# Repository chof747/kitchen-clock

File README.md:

# Kitchen Clock Project

This project is building a kitchen glock with the following functions:

- Servo driven largely visible glock gauge
- Alarm functions that can be sequenced easily
- Temperature control of a stove or oven
- Integration into home automation systems with HA and/or MQTT
- Ringing alarm function

the project will contain all the necessary electrical and housing components.

## PCB

**v1.0**: Initial version of PCB sent to production on 22.07.2024
**v1.1**

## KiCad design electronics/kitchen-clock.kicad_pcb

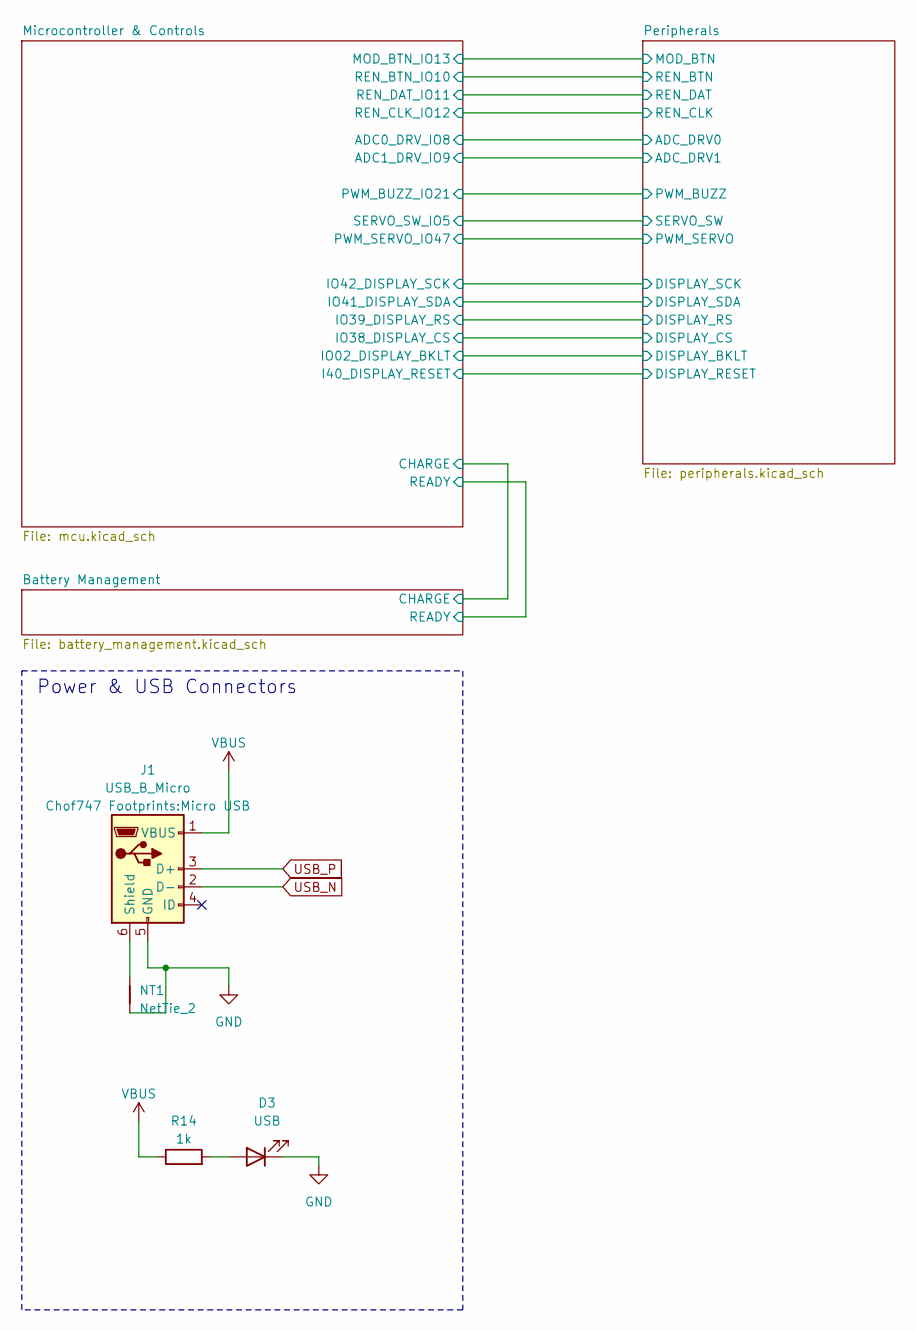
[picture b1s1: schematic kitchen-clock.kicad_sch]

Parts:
D3: USB; LED_D3.0mm
J1: USB_B_Micro; Micro USB
NT1: NetTie_2; NetTie-2_SMD_Pad0.5mm
R14: 1k; R_0603_1608Metric_Pad0.98x0.95mm_HandSolder

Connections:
GND: D3.1 (K), J1.5 (GND), NT1.1; also elsewhere on the board
unnamed: D3.2 (A), R14.2
unnamed: J1.6 (Shield), NT1.2
USB_N: J1.2 (D-); also elsewhere on the board
USB_P: J1.3 (D+); also elsewhere on the board
VBUS: J1.1 (VBUS), R14.1; also elsewhere on the board

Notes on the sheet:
Power & USB Connectors

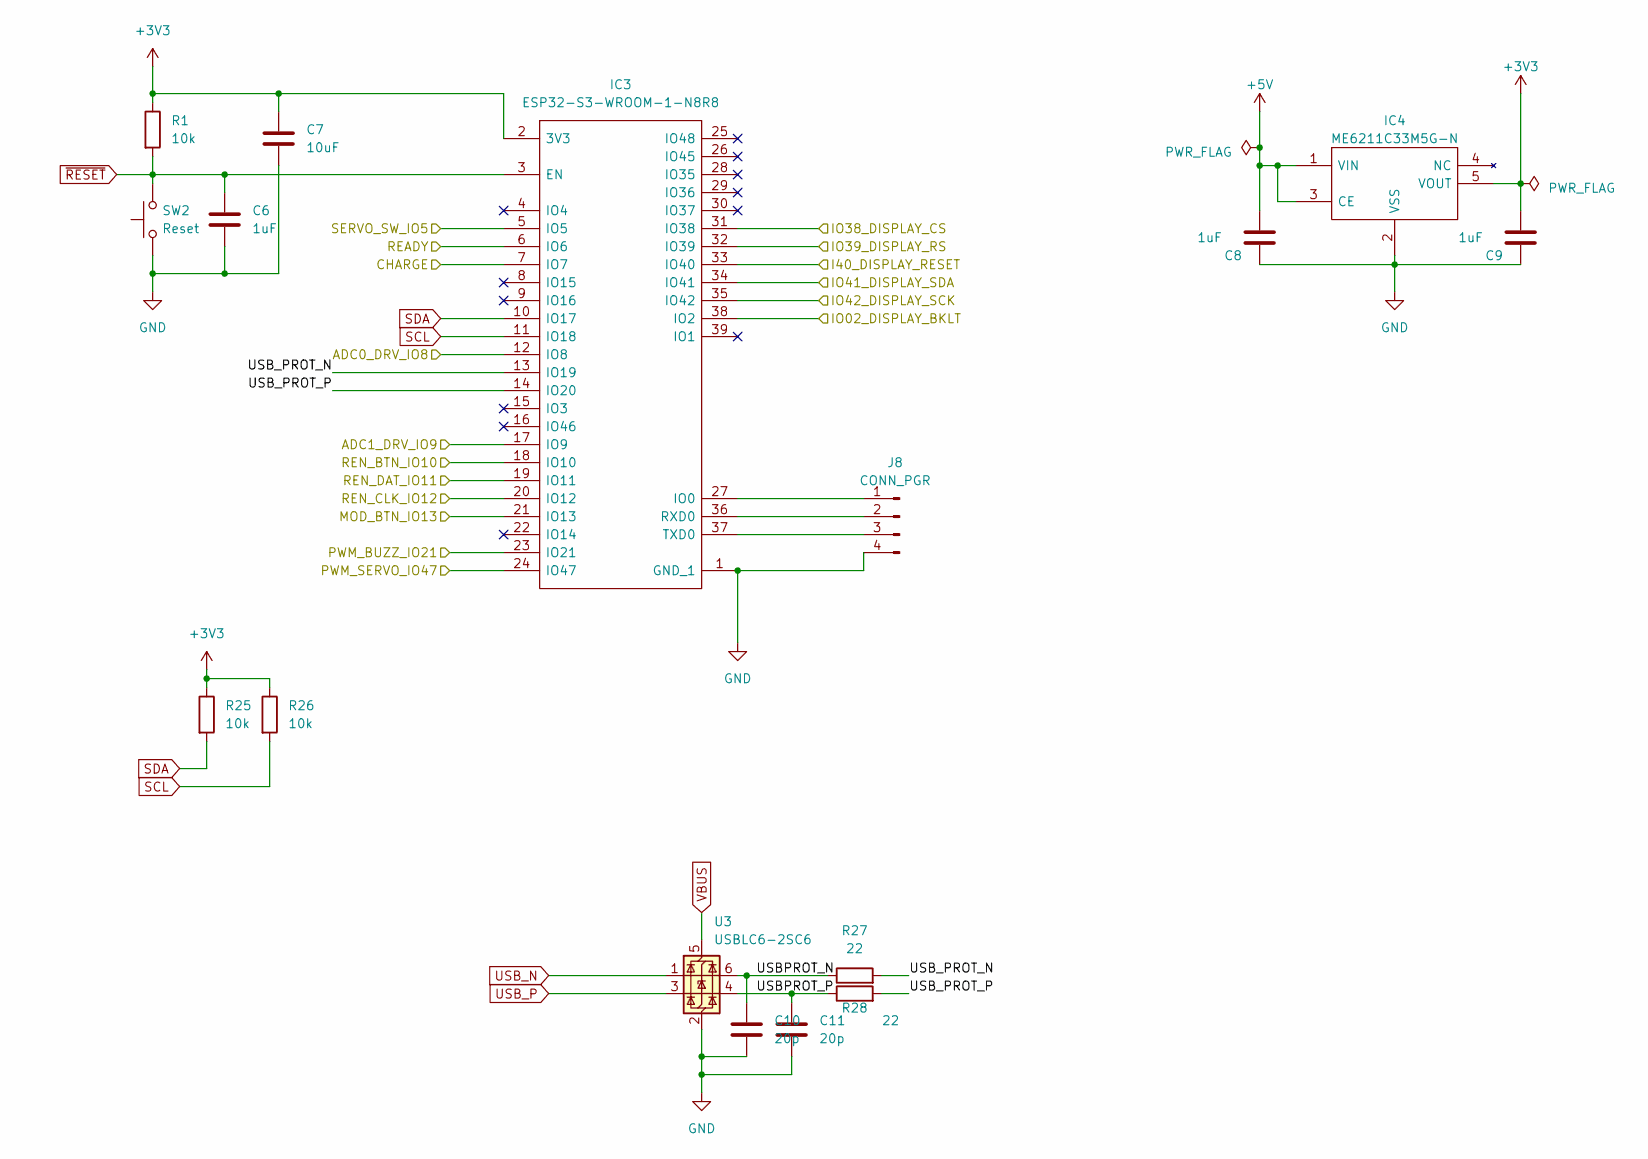
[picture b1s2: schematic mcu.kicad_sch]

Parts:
C6, C8, C9: 1uF; C_0603_1608Metric_Pad1.08x0.95mm_HandSolder
C7: 10uF; C_0603_1608Metric_Pad1.08x0.95mm_HandSolder
C10, C11: 20p; C_0603_1608Metric_Pad1.08x0.95mm_HandSolder
IC3: ESP32-S3-WROOM-1-N8R8; ESP32S3WROOM1N8R8; Manufacturer_Part_Number ESP32-S3-WROOM-1-N8R8; Mouser Part Number 356-EP32S3WROOM1N8R8
IC4: ME6211C33M5G-N; SOT95P270X145-5N; Manufacturer_Part_Number ME6211C33M5G-N
J8: CONN_PGR; PinSocket_1x04_P2.54mm_Vertical
R1, R25, R26: 10k; R_0603_1608Metric_Pad0.98x0.95mm_HandSolder
R27, R28: 22; R_0603_1608Metric_Pad0.98x0.95mm_HandSolder
SW2: Reset; 1TS003B-2500-3500A-CT (SMD Right Angle Tactile Switch)
U3: USBLC6-2SC6; SOT-23-6

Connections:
+3V3: C7.1, C9.1, IC3.2 (3V3), IC4.5 (VOUT), R1.1, R25.1, R26.1; also elsewhere on the board
+5V: C8.1, IC4.1 (VIN), IC4.3 (CE); also elsewhere on the board
/Battery Management/CHARGE: IC3.7 (IO7); also elsewhere on the board
/Battery Management/READY: IC3.6 (IO6); also elsewhere on the board
/Microcontroller & Controls/ADC0_DRV_IO8: IC3.12 (IO8); also elsewhere on the board
/Microcontroller & Controls/ADC1_DRV_IO9: IC3.17 (IO9); also elsewhere on the board
/Microcontroller & Controls/I40_DISPLAY_RESET: IC3.33 (IO40); also elsewhere on the board
/Microcontroller & Controls/IO02_DISPLAY_BKLT: IC3.38 (IO2); also elsewhere on the board
/Microcontroller & Controls/IO38_DISPLAY_CS: IC3.31 (IO38); also elsewhere on the board
/Microcontroller & Controls/IO39_DISPLAY_RS: IC3.32 (IO39); also elsewhere on the board
/Microcontroller & Controls/IO41_DISPLAY_SDA: IC3.34 (IO41); also elsewhere on the board
/Microcontroller & Controls/IO42_DISPLAY_SCK: IC3.35 (IO42); also elsewhere on the board
/Microcontroller & Controls/MOD_BTN_IO13: IC3.21 (IO13); also elsewhere on the board
/Microcontroller & Controls/PWM_BUZZ_IO21: IC3.23 (IO21); also elsewhere on the board
/Microcontroller & Controls/PWM_SERVO_IO47: IC3.24 (IO47); also elsewhere on the board
/Microcontroller & Controls/REN_BTN_IO10: IC3.18 (IO10); also elsewhere on the board
/Microcontroller & Controls/REN_CLK_IO12: IC3.20 (IO12); also elsewhere on the board
/Microcontroller & Controls/REN_DAT_IO11: IC3.19 (IO11); also elsewhere on the board
/Microcontroller & Controls/SERVO_SW_IO5: IC3.5 (IO5); also elsewhere on the board
/Microcontroller & Controls/USBPROT_N: C10.1, R27.1, U3.6 (I/O1)
/Microcontroller & Controls/USBPROT_P: C11.1, R28.1, U3.4 (I/O2)
/Microcontroller & Controls/USB_PROT_N: IC3.13 (IO19), R27.2
/Microcontroller & Controls/USB_PROT_P: IC3.14 (IO20), R28.2
GND: C6.2, C7.2, C8.2, C9.2, C10.2, C11.2, IC3.1 (GND_1), IC4.2 (VSS), J8.4, SW2.1, U3.2 (GND); also elsewhere on the board
unnamed: IC3.27 (IO0), J8.1
unnamed: IC3.36 (RXD0), J8.2
unnamed: IC3.37 (TXD0), J8.3
SCL: IC3.11 (IO18), R26.2; also elsewhere on the board
SDA: IC3.10 (IO17), R25.2; also elsewhere on the board
USB_N: U3.1 (I/O1); also elsewhere on the board
USB_P: U3.3 (I/O2); also elsewhere on the board
VBUS: U3.5 (VBUS); also elsewhere on the board
~RESET: C6.1, IC3.3 (EN), R1.2, SW2.2; also elsewhere on the board

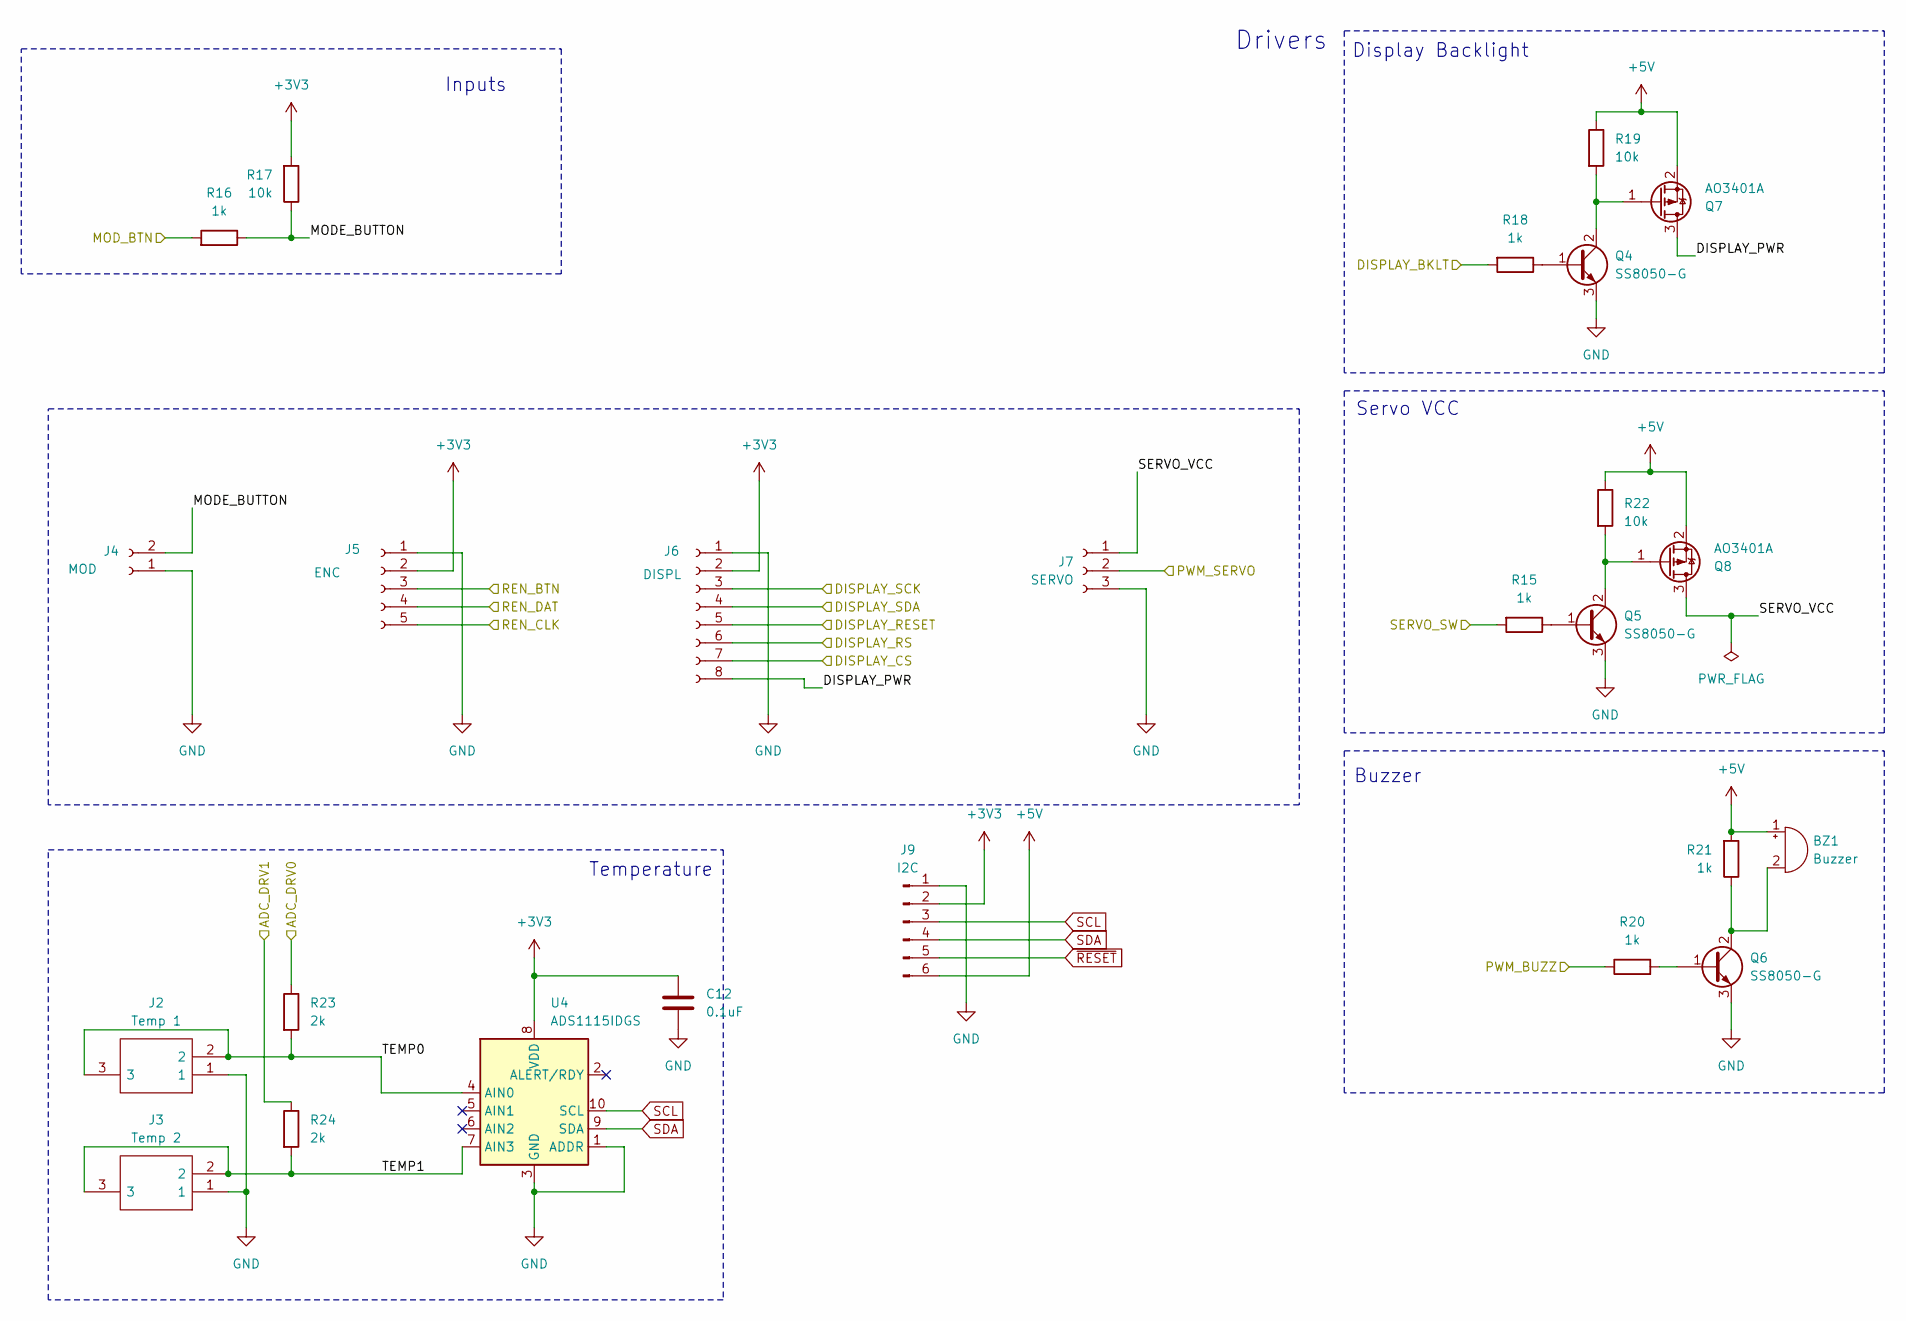
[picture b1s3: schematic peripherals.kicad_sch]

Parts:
BZ1: Buzzer; PS1240P02BT
C12: 0.1uF; C_0603_1608Metric_Pad1.08x0.95mm_HandSolder
J2: Temp 1; MJ2509N; Manufacturer_Part_Number MJ-2509N; Mouser Part Number 490-MJ-2509N
J3: Temp 2; MJ2509N; Manufacturer_Part_Number MJ-2509N; Mouser Part Number 490-MJ-2509N
J4: MOD; PinSocket_1x02_P2.54mm_Vertical
J5: ENC; PinSocket_1x05_P2.54mm_Vertical
J6: DISPL; PinSocket_1x08_P2.54mm_Vertical
J7: SERVO; PinSocket_1x03_P2.54mm_Vertical
J9: I2C; PinHeader_1x06_P2.54mm_Vertical
Q4, Q5, Q6: SS8050-G; SOT-23
Q7, Q8: AO3401A; SOT-23
R15, R16, R18, R20, R21: 1k; R_0603_1608Metric_Pad0.98x0.95mm_HandSolder
R17, R19, R22: 10k; R_0603_1608Metric_Pad0.98x0.95mm_HandSolder
R23, R24: 2k; R_0603_1608Metric_Pad0.98x0.95mm_HandSolder
U4: ADS1115IDGS; TSSOP-10_3x3mm_P0.5mm

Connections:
+3V3: C12.1, J5.2, J6.2, J9.2, R17.2, U4.8 (VDD); also elsewhere on the board
+5V: BZ1.1 (+), J9.6, Q7.2 (S), Q8.2 (S), R19.1, R21.2, R22.1; also elsewhere on the board
/Microcontroller & Controls/ADC0_DRV_IO8: R23.1; also elsewhere on the board
/Microcontroller & Controls/ADC1_DRV_IO9: R24.1; also elsewhere on the board
/Microcontroller & Controls/I40_DISPLAY_RESET: J6.5; also elsewhere on the board
/Microcontroller & Controls/IO02_DISPLAY_BKLT: R18.2; also elsewhere on the board
/Microcontroller & Controls/IO38_DISPLAY_CS: J6.7; also elsewhere on the board
/Microcontroller & Controls/IO39_DISPLAY_RS: J6.6; also elsewhere on the board
/Microcontroller & Controls/IO41_DISPLAY_SDA: J6.4; also elsewhere on the board
/Microcontroller & Controls/IO42_DISPLAY_SCK: J6.3; also elsewhere on the board
/Microcontroller & Controls/MOD_BTN_IO13: R16.2; also elsewhere on the board
/Microcontroller & Controls/PWM_BUZZ_IO21: R20.1; also elsewhere on the board
/Microcontroller & Controls/PWM_SERVO_IO47: J7.2; also elsewhere on the board
/Microcontroller & Controls/REN_BTN_IO10: J5.3; also elsewhere on the board
/Microcontroller & Controls/REN_CLK_IO12: J5.5; also elsewhere on the board
/Microcontroller & Controls/REN_DAT_IO11: J5.4; also elsewhere on the board
/Microcontroller & Controls/SERVO_SW_IO5: R15.2; also elsewhere on the board
/Peripherals/DISPLAY_PWR: J6.8, Q7.3 (D)
/Peripherals/MODE_BUTTON: J4.2, R16.1, R17.1
/Peripherals/SERVO_VCC: J7.1, Q8.3 (D)
/Peripherals/TEMP0: J2.2, J2.3, R23.2, U4.4 (AIN0)
/Peripherals/TEMP1: J3.2, J3.3, R24.2, U4.7 (AIN3)
GND: C12.2, J2.1, J3.1, J4.1, J5.1, J6.1, J7.3, J9.1, Q4.3 (E), Q5.3 (E), Q6.3 (E), U4.1 (ADDR), U4.3 (GND); also elsewhere on the board
unnamed: BZ1.2 (-), Q6.2 (C), R21.1
unnamed: Q4.1 (B), R18.1
unnamed: Q4.2 (C), Q7.1 (G), R19.2
unnamed: Q5.1 (B), R15.1
unnamed: Q5.2 (C), Q8.1 (G), R22.2
unnamed: Q6.1 (B), R20.2
SCL: J9.3, U4.10 (SCL); also elsewhere on the board
SDA: J9.4, U4.9 (SDA); also elsewhere on the board
~RESET: J9.5; also elsewhere on the board

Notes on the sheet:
Temperature
Servo VCC
Inputs
Drivers
Buzzer
Display Backlight

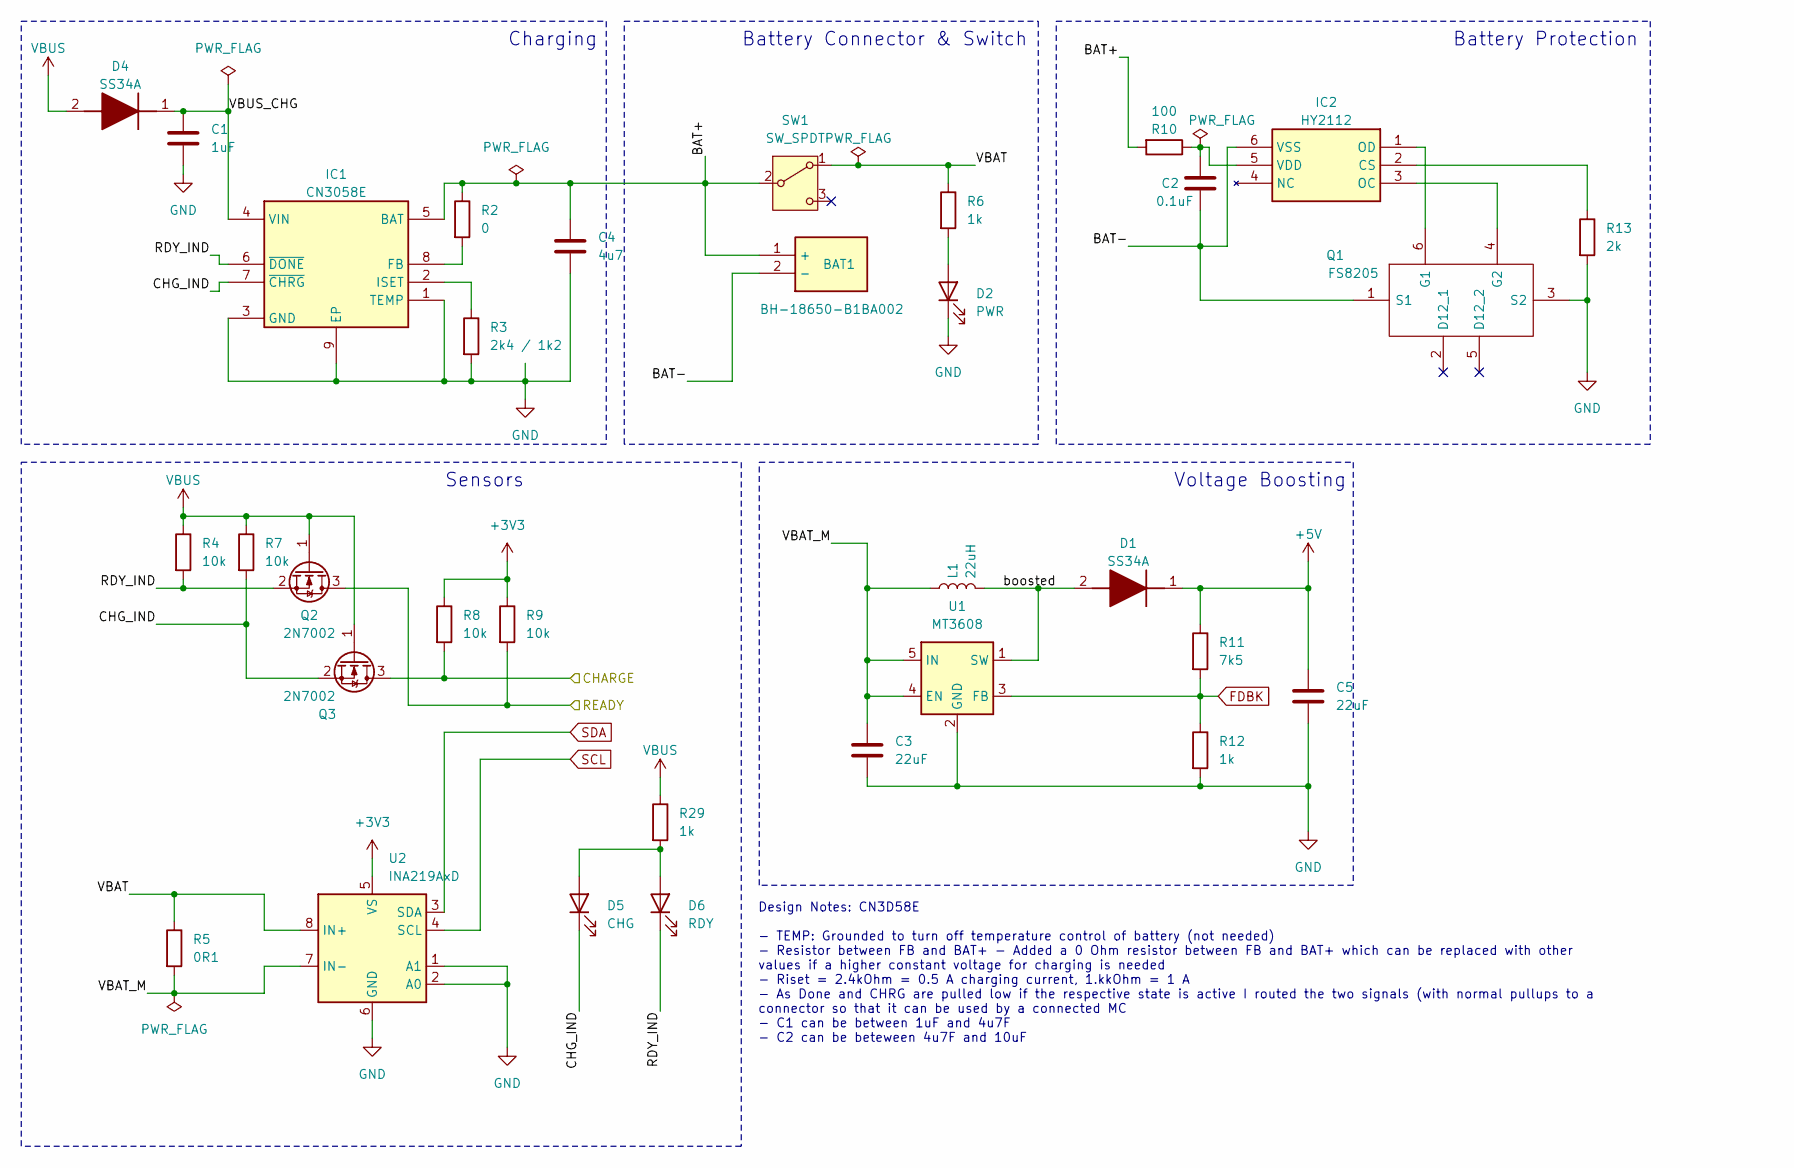
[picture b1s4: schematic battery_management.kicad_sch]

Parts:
BAT1: BH-18650-B1BA002; BH18650B1BA002; Manufacturer_Part_Number BH-18650-B1BA002
C1: 1uF; C_0603_1608Metric_Pad1.08x0.95mm_HandSolder
C2: 0.1uF; C_0603_1608Metric_Pad1.08x0.95mm_HandSolder
C3, C5: 22uF; C_1206_3216Metric_Pad1.33x1.80mm_HandSolder
C4: 4u7; C_0603_1608Metric_Pad1.08x0.95mm_HandSolder
D1, D4: SS34A; DIOM5026X262N; Manufacturer_Part_Number SS34A
D2: PWR; LED_D3.0mm
D5: CHG; LED_D3.0mm
D6: RDY; LED_D3.0mm
IC1: CN3058E; SOIC127P600X175-9N; Manufacturer_Part_Number CN3058E
IC2: HY2112; SOT95P280X145-6N; Manufacturer_Part_Number HY2112
L1: 22uH; SMD0740
Q1: FS8205; Manufacturer_Part_Number FS8205
Q2, Q3: 2N7002; SOT-23
R2: 0; R_0603_1608Metric_Pad0.98x0.95mm_HandSolder
R3: 2k4 / 1k2; R_0603_1608Metric_Pad0.98x0.95mm_HandSolder
R4, R7, R8, R9: 10k; R_0603_1608Metric_Pad0.98x0.95mm_HandSolder
R5: 0R1; R_2512_6332Metric_Pad1.40x3.35mm_HandSolder
R6, R12, R29: 1k; R_0603_1608Metric_Pad0.98x0.95mm_HandSolder
R10: 100; R_0603_1608Metric_Pad0.98x0.95mm_HandSolder
R11: 7k5; R_0603_1608Metric_Pad0.98x0.95mm_HandSolder
R13: 2k; R_0603_1608Metric_Pad0.98x0.95mm_HandSolder
SW1: SW_SPDT; Slide-switch-SS-12D11L7
U1: MT3608; SOT-23-6
U2: INA219AxD; SOIC-8_3.9x4.9mm_P1.27mm

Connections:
+3V3: R8.1, R9.1, U2.5 (VS); also elsewhere on the board
+5V: C5.1, D1.1 (K), R11.1; also elsewhere on the board
/Battery Management/BAT+: BAT1.1 (+), C4.1, IC1.5 (BAT), R2.1, R10.2, SW1.2 (B)
/Battery Management/BAT-: BAT1.2 (-), C2.2, IC2.6 (VSS), Q1.1 (S1)
/Battery Management/CHARGE: Q3.3 (D), R8.2; also elsewhere on the board
/Battery Management/CHG_IND: D5.1 (K), IC1.7 (~CHRG), Q3.2 (S), R7.2
/Battery Management/RDY_IND: D6.1 (K), IC1.6 (~DONE), Q2.2 (S), R4.2
/Battery Management/READY: Q2.3 (D), R9.2; also elsewhere on the board
/Battery Management/VBAT: R5.1, R6.1, SW1.1 (A), U2.8 (IN+)
/Battery Management/VBAT_M: C3.1, L1.1, R5.2, U1.4 (EN), U1.5 (IN), U2.7 (IN-)
/Battery Management/VBUS_CHG: C1.1, D4.1 (K), IC1.4 (VIN)
/Battery Management/boosted: D1.2 (A), L1.2, U1.1 (SW)
FDBK: R11.2, R12.1, U1.3 (FB)
GND: C1.2, C3.2, C4.2, C5.2, D2.1 (K), IC1.1 (TEMP), IC1.3 (GND), IC1.9 (EP), Q1.3 (S2), R3.2, R12.2, R13.2, U1.2 (GND), U2.1 (A1), U2.2 (A0), U2.6 (GND); also elsewhere on the board
unnamed: D2.2 (A), R6.2
unnamed: D5.2 (A), D6.2 (A), R29.2
unnamed: IC1.8 (FB), R2.2
unnamed: IC1.2 (ISET), R3.1
unnamed: IC2.2 (CS), R13.1
unnamed: IC2.3 (OC), Q1.4 (G2)
unnamed: IC2.1 (OD), Q1.6 (G1)
unnamed: C2.1, IC2.5 (VDD), R10.1
SCL: U2.4 (SCL); also elsewhere on the board
SDA: U2.3 (SDA); also elsewhere on the board
VBUS: D4.2 (A), Q2.1 (G), Q3.1 (G), R4.1, R7.1, R29.1; also elsewhere on the board

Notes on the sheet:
Design Notes: CN3D58E - TEMP: Grounded to turn off temperature control of battery (not needed) - Resistor between FB and BAT+ - Added a 0 Ohm resistor between FB and BAT+ which can be replaced with other values if a higher constant voltage for charging is needed - Riset = 2.4kOhm = 0.5 A charging c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
Battery Protection
Battery Connector & Switch
Voltage Boosting
Charging
Sensors

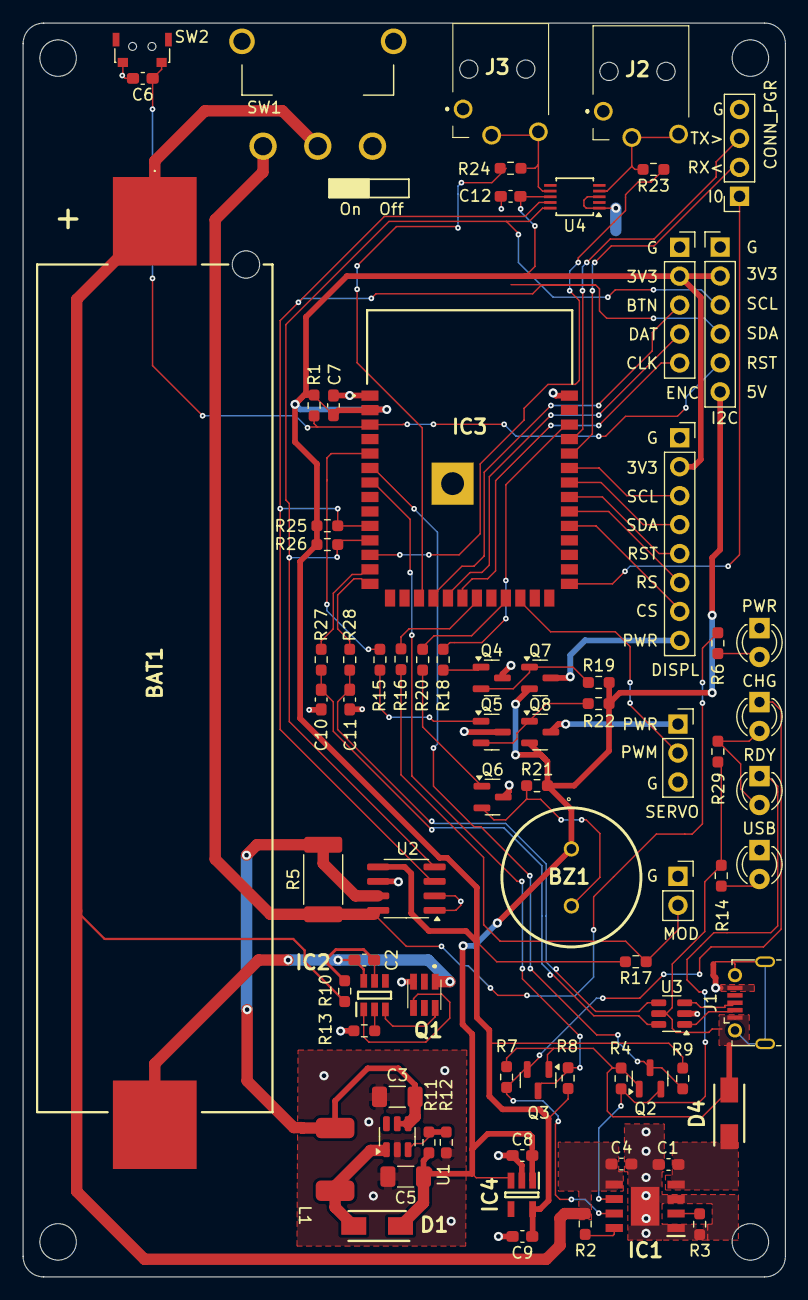
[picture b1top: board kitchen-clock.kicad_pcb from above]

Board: 2 copper layers, 66.9 x 110.0 mm, 78 parts (0 on the bottom side), 63 nets.

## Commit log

2024-04-30 Initial commit with dial and clock
2024-05-15 Further developing of the 3d models: - completed socket, gauge, base and dial - added assembly file - updated documentation
2024-05-20 Added template for tft display
2024-05-20 Further progress on 3d model: - Finished socket - Added base - Minor changes to dial before first print
2024-05-20 recreation of real servo Horn
2024-05-20 Changed shape of servo horn to actual shape
2024-05-20 Added firmware and first version of controlling tools
2024-06-08 added test directory in 3dmodel and added it to .gitignore for 3dmodel
2024-06-08 Next update to 3dmodel
2024-06-08 Added script and hook for stl generatio upon pushing to the main branch
2024-06-08 changed to freecad image
2024-06-08 removed latest tag
2024-06-08 corrected container spec
2024-06-08 revert to original version
2024-06-08 ensure exit code 0
2024-06-08 change stl zip generation and upload
2024-06-09 Added nuts and model for rotary encoder
2024-06-09 Added .gitignore for electronics
2024-06-09 initialized kicad project
2024-06-09 draft of schematics done
2024-06-16 First draft of schematic and PCB of controller board
2024-06-21 changed footprint of reset button
2024-06-21 added kicad cache directory to .gitignore
2024-06-21 Model update
2024-06-21 added knob for Rotary Encoder
2024-06-24 performed CRC check and fixed errors
2024-06-24 added stlignore file to components directory to exclude single freecad files from processing
2024-06-24 further progress on the model
2024-07-18 Added design decision document
2024-07-18 Performed CRC and DRC on board + corrections
2024-07-20 added production folder to .gitignore
2024-07-20 added _autsave*
2024-07-20 fixed reference issues with 3d models
2024-07-20 minor change in project file for kicad
2024-07-20 added kibot automation
2024-07-20 added pcb v1.0 to README
2024-07-20 workspace file fix
2024-08-08 added testing firmware and platform.ini
2024-09-14 firmware updates
2024-09-14 Adjustments after first test print of base
2024-09-14 added adafruit library for tfts
2024-09-16 Added battery voltage levels
2024-09-16 Added statuscontroller and status region
2024-09-21 started with v1.1 pcb fixes
2024-09-21 updated pcb 3d file with correct battery model
2024-09-21 added n
2024-09-26 first upload of new component assembly and case
2024-09-26 updates to 3d case model
2024-09-26 update on pcb design
2024-09-26 fixing display issue
2024-10-13 added v1.1 board to readme
2024-10-13 added lfs tracking
2024-10-13 new base and scaffold based on assembly
2024-10-14 fixed indexing issues with base profile of scaffold
2024-10-14 started working on front component
2024-10-15 added gauge to assembly and fixed servo real dimensions
2024-10-18 update to freecad 1.0rc2 and changed front config
2024-10-18 corrected unintended void on the lift side of the pcb which distorted the symmetry
2024-10-18 adjusted assembly
2024-10-20 assembly of components completed
2024-10-20 added servo to assembly
    - Corrected Servo file servo-horn
    - Reduced thickness of gauge
    - Added servo to assembly
2024-10-25 Intermediate commit
2024-10-25 Version 1 of front and base done
2024-10-26 Added bracket for display and servo
2024-10-28 Added chamfers and filet to front
2024-10-28 corrected display pcb overstand to 0
2024-10-31 Recentered screen and assembly
2024-11-27 Addded start page, control unit and images
2024-11-27 final modifications for printing
2024-11-29 Added version to build flags
2024-12-04 added startregion with logo for startup
2024-12-04 added startregion.cpp
2024-12-04 added menu icons for main menu
2024-12-04 changed setup of app to separate files
    also added icons to display_views.h
2024-12-04 minor updates
2024-12-04 updated debugging speed
2025-01-05 firmware with first working version of menu
2025-01-18 Added Temp Controller
    - Added temp region and temp controller
    - Included NTC on top of ADS
    - Added fonts for temp region
    - Fixed issues with region deactivation
    - Added controll unit interface to simplify controller takeover of controls
2025-01-19 Renamed TempController into TempMainController to allow more controllers
2025-02-07 Configure ADC channel via config.h and added macro to populate channels
2025-02-14 Updates on main temperature window and added temperature monitor controller and region
